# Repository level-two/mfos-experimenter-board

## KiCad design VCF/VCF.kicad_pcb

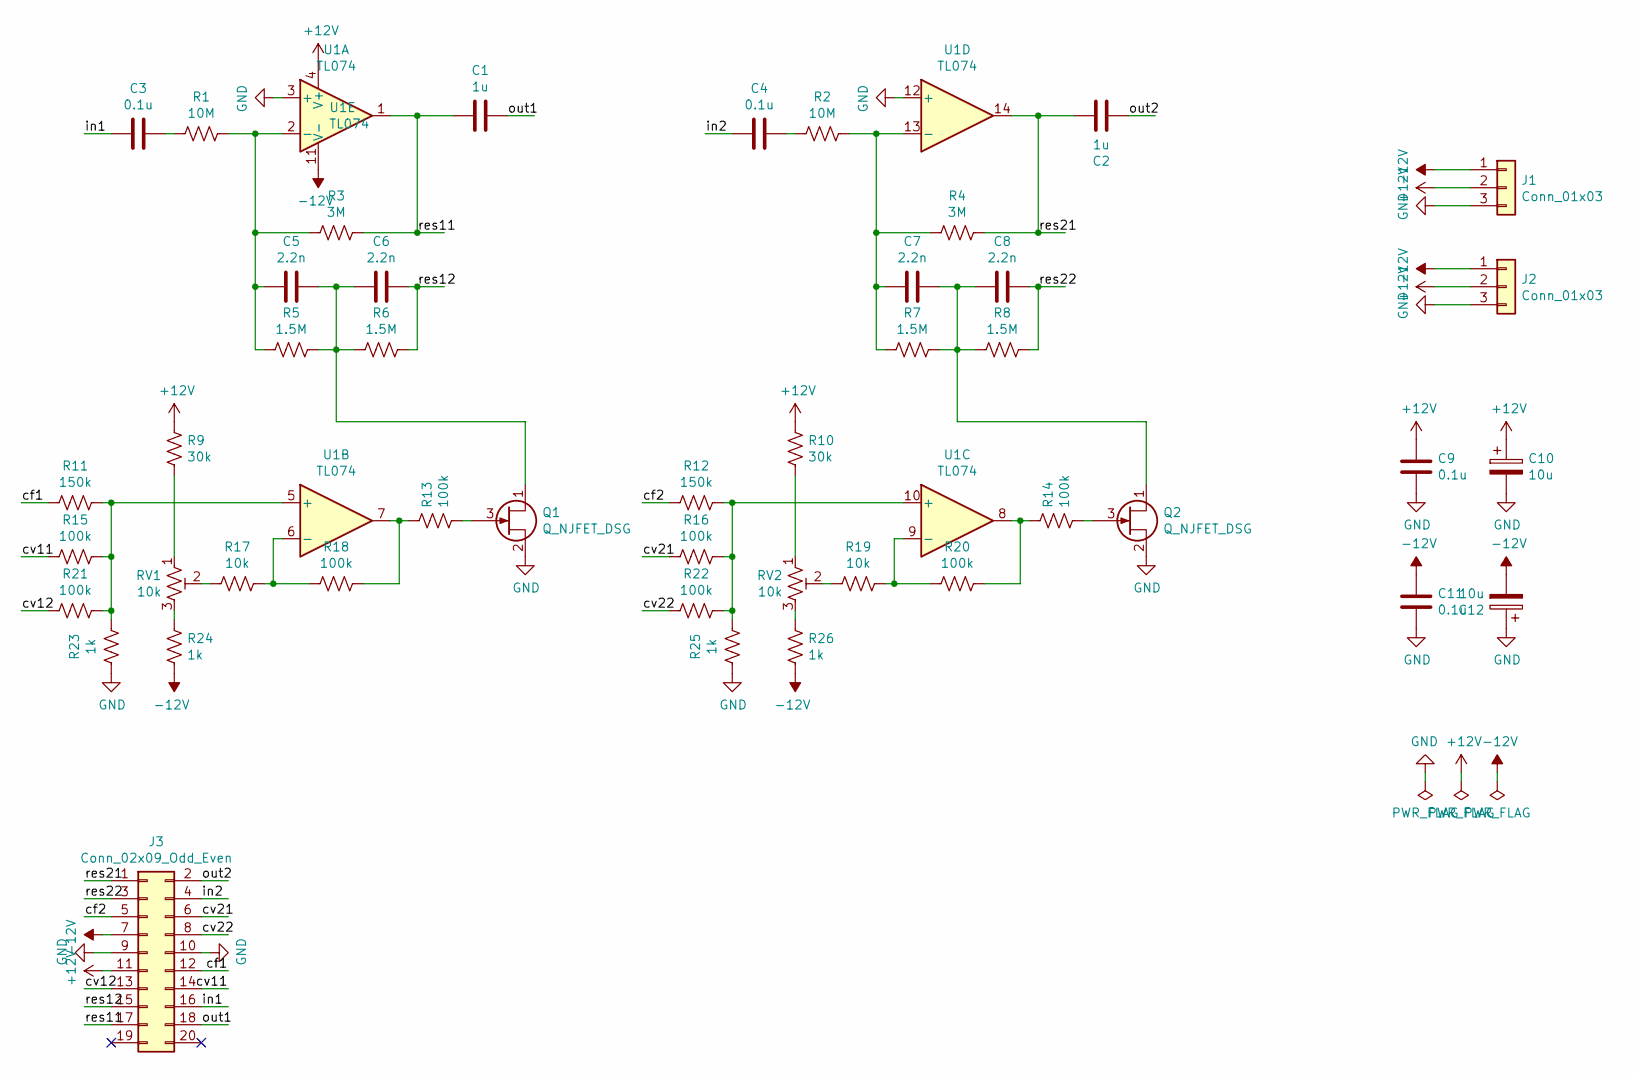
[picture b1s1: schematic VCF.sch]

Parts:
C1, C2: 1u; C_0603_1608Metric
C3, C4, C9, C11: 0.1u; C_0603_1608Metric
C5, C6, C7, C8: 2.2n; C_0402_1005Metric
C10, C12: 10u; C_Elec_6.3x5.4
J1, J2: Conn_01x03; PinHeader_1x03_P2.54mm_Horizontal
J3: Conn_02x09_Odd_Even; PinHeader_2x10_P2.54mm_Horizontal
Q1, Q2: Q_NJFET_DSG; TSOT-23
R1, R2: 10M; R_0402_1005Metric
R3, R4: 3M; R_0402_1005Metric
R5, R6, R7, R8: 1.5M; R_0402_1005Metric
R9, R10: 30k; R_0402_1005Metric
R11, R12: 150k; R_0402_1005Metric
R13, R14, R15, R16, R18, R20, R21, R22: 100k; R_0402_1005Metric
R17, R19: 10k; R_0402_1005Metric
R23, R24, R25, R26: 1k; R_0402_1005Metric
RV1, RV2: 10k; 3302
U1: TL074; SOIC-14_3.9x8.7mm_P1.27mm

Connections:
+12V: C9.1, C10.1, J1.2, J2.2, J3.11, R9.1, R10.1, U1.4 (V+)
-12V: C11.1, C12.2, J1.1, J2.1, J3.7, R24.2, R26.2, U1.11 (V-)
/cf1: J3.12, R11.2
/cf2: J3.5, R12.2
/cv11: J3.14, R15.2
/cv12: J3.13, R21.2
/cv21: J3.6, R16.2
/cv22: J3.8, R22.2
/in1: C3.2, J3.16
/in2: C4.2, J3.4
/out1: C1.1, J3.18
/out2: C2.1, J3.2
/res11: C1.2, J3.17, R3.1, U1.1
/res12: C6.1, J3.15, R6.1
/res21: C2.2, J3.1, R4.1, U1.14
/res22: C8.1, J3.3, R8.1
GND: C9.2, C10.2, C11.2, C12.1, J1.3, J2.3, J3.9, J3.10, Q1.2 (S), Q2.2 (S), R23.2, R25.2, U1.3 (+), U1.12 (+)
unnamed: C3.1, R1.2
unnamed: C4.1, R2.2
unnamed: C5.1, C6.2, Q1.1 (D), R5.1, R6.2
unnamed: C5.2, R1.1, R3.2, R5.2, U1.2 (-)
unnamed: C7.1, C8.2, Q2.1 (D), R7.1, R8.2
unnamed: C7.2, R2.1, R4.2, R7.2, U1.13 (-)
unnamed: Q1.3 (G), R13.2
unnamed: Q2.3 (G), R14.2
unnamed: R9.2, RV1.1
unnamed: R10.2, RV2.1
unnamed: R11.1, R15.1, R21.1, R23.1, U1.5 (+)
unnamed: R12.1, R16.1, R22.1, R25.1, U1.10 (+)
unnamed: R13.1, R18.2, U1.7
unnamed: R14.1, R20.2, U1.8
unnamed: R17.1, RV1.2
unnamed: R17.2, R18.1, U1.6 (-)
unnamed: R19.1, RV2.2
unnamed: R19.2, R20.1, U1.9 (-)
unnamed: R24.1, RV1.3
unnamed: R26.1, RV2.3

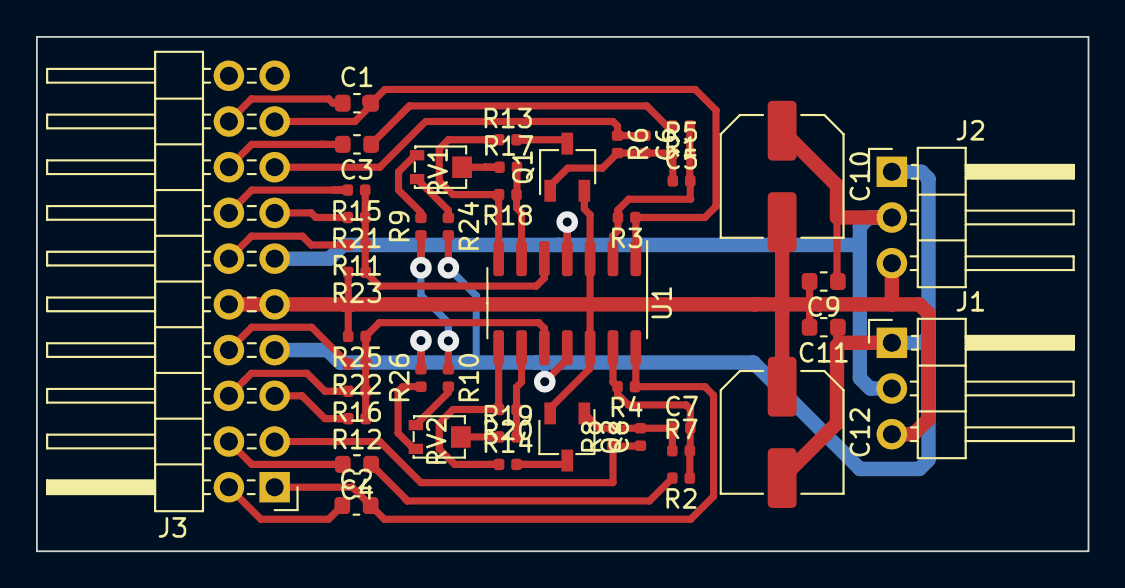
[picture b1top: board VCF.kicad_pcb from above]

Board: 2 copper layers, 58.4 x 28.6 mm, 46 parts (0 on the bottom side), 37 nets.

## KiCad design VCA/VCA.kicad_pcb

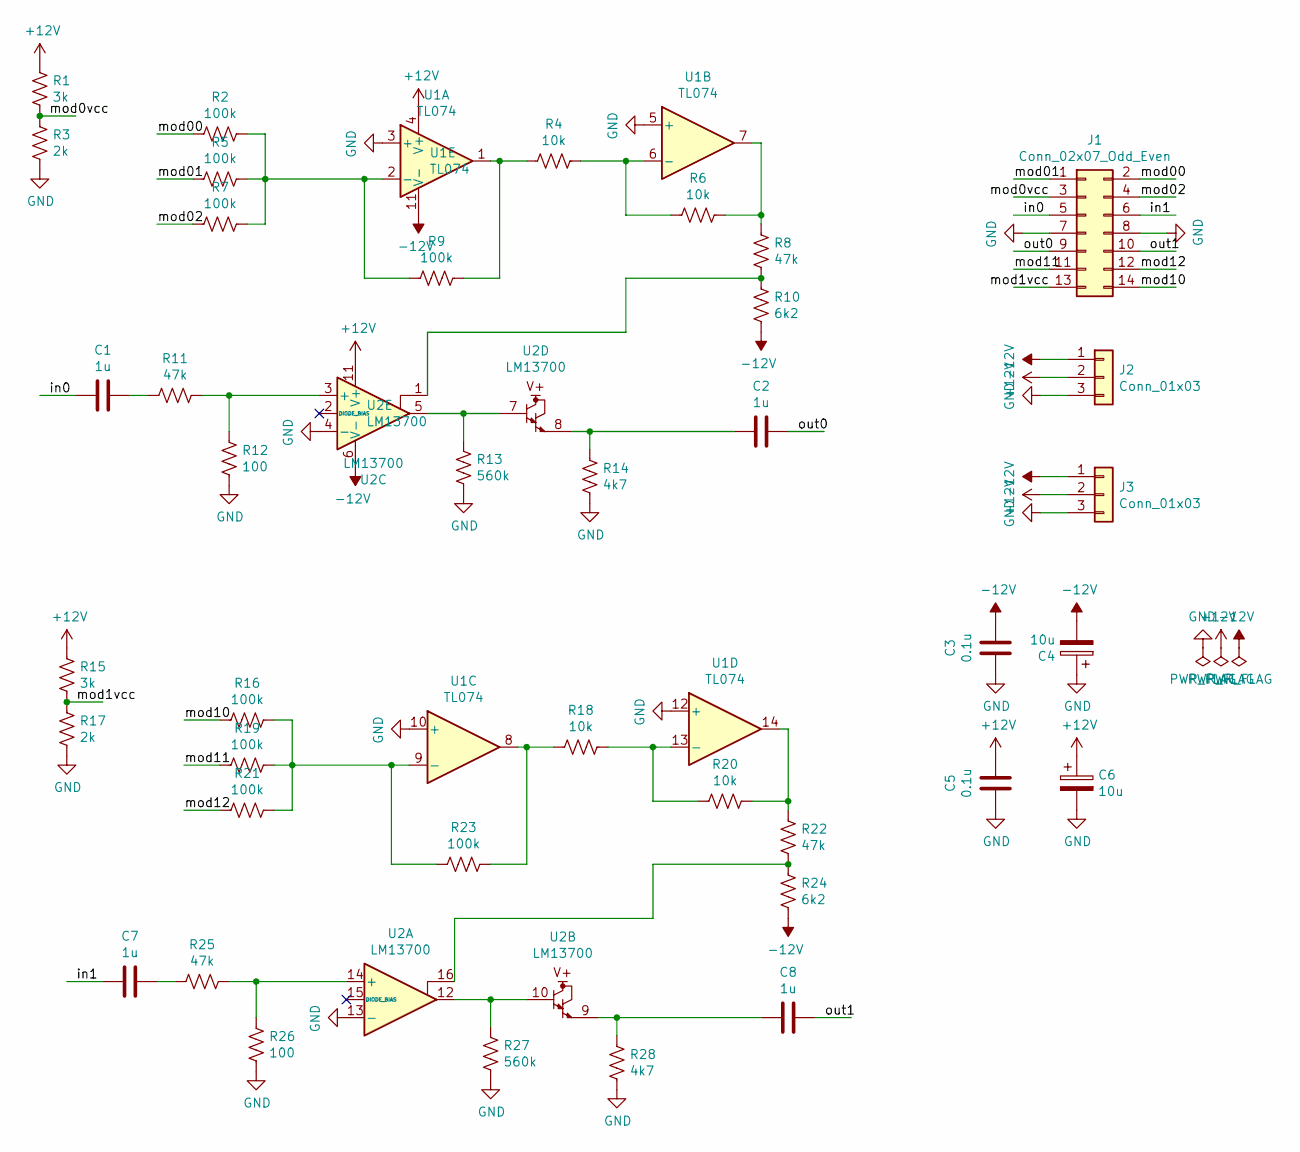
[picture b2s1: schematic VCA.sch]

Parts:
C1, C2, C7, C8: 1u; C_0603_1608Metric
C3, C5: 0.1u; C_0603_1608Metric
C4, C6: 10u; CP_Elec_6.3x5.4
J1: Conn_02x07_Odd_Even; IDC-Header_2x07_P2.54mm_Horizontal
J2, J3: Conn_01x03; PinHeader_1x03_P2.54mm_Horizontal
R1, R15: 3k; R_0402_1005Metric
R2, R5, R7, R9, R16, R19, R21, R23: 100k; R_0402_1005Metric
R3, R17: 2k; R_0402_1005Metric
R4, R6, R18, R20: 10k; R_0402_1005Metric
R8, R11, R22, R25: 47k; R_0402_1005Metric
R10, R24: 6k2; R_0402_1005Metric
R12, R26: 100; R_0402_1005Metric
R13, R27: 560k; R_0402_1005Metric
R14, R28: 4k7; R_0402_1005Metric
U1: TL074; SOIC-14_3.9x8.7mm_P1.27mm
U2: LM13700; DIP-16_W7.62mm

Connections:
+12V: C5.1, C6.1, J2.2, J3.2, R1.1, R15.1, U1.4 (V+), U2.11 (V+)
-12V: C3.1, C4.2, J2.1, J3.1, R10.2, R24.2, U1.11 (V-), U2.6 (V-)
/in0: C1.2, J1.5
/in1: C7.2, J1.6
/mod00: J1.2, R2.1
/mod0vcc: J1.3, R1.2, R3.1
/mod01: J1.1, R5.1
/mod1vcc: J1.13, R15.2, R17.1
/mod02: J1.4, R7.1
/mod10: J1.14, R16.1
/mod11: J1.11, R19.1
/mod12: J1.12, R21.1
/out0: C2.1, J1.9
/out1: C8.1, J1.10
GND: C3.2, C4.1, C5.2, C6.2, J1.7, J1.8, J2.3, J3.3, R3.2, R12.1, R13.2, R14.2, R17.2, R26.1, R27.2, R28.2, U1.3 (+), U1.5 (+), U1.10 (+), U1.12 (+), U2.4 (-), U2.13 (-)
unnamed: C1.1, R11.1
unnamed: C2.2, R14.1, U2.8
unnamed: C7.1, R25.1
unnamed: C8.2, R28.1, U2.9
unnamed: R2.2, R5.2, R7.2, R9.1, U1.2 (-)
unnamed: R4.1, R9.2, U1.1
unnamed: R4.2, R6.1, U1.6 (-)
unnamed: R6.2, R8.1, U1.7
unnamed: R8.2, R10.1, U2.1
unnamed: R11.2, R12.2, U2.3 (+)
unnamed: R13.1, U2.5, U2.7
unnamed: R16.2, R19.2, R21.2, R23.1, U1.9 (-)
unnamed: R18.1, R23.2, U1.8
unnamed: R18.2, R20.1, U1.13 (-)
unnamed: R20.2, R22.1, U1.14
unnamed: R22.2, R24.1, U2.16
unnamed: R25.2, R26.2, U2.14 (+)
unnamed: R27.1, U2.10, U2.12

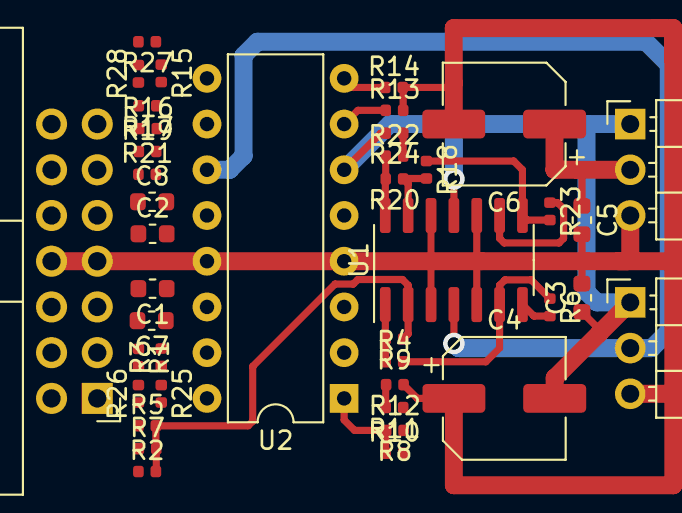
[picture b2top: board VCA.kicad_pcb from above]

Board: 2 copper layers, 41 parts (0 on the bottom side), 33 nets.

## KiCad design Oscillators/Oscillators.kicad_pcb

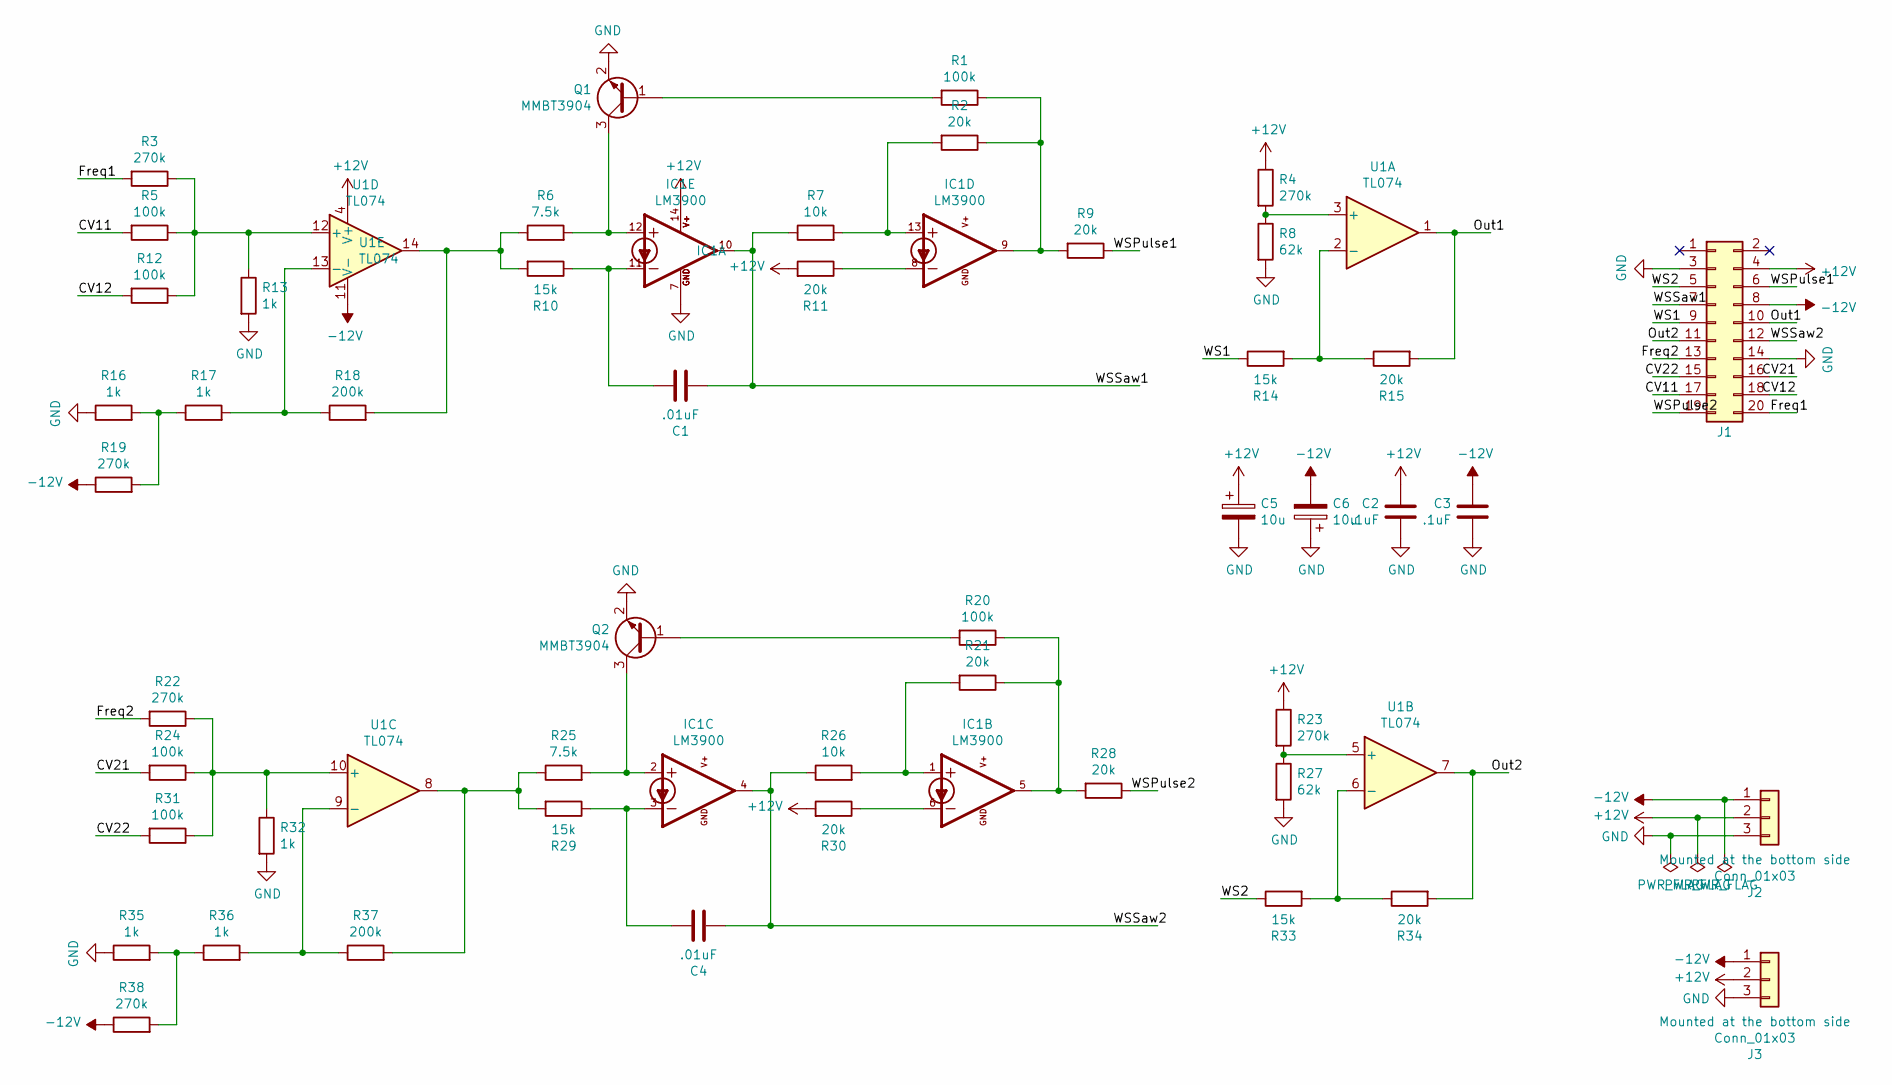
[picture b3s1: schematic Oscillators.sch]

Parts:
C1, C4: .01uF; C_0402_1005Metric
C2, C3: .1uF; C_0603_1608Metric
C5, C6: 10u; C_Elec_6.3x5.4
IC1: LM3900; SOIC-14_3.9x8.7mm_P1.27mm
J1: Conn_02x09_Odd_Even; PinHeader_2x10_P2.54mm_Horizontal
J2, J3: Conn_01x03; PinSocket_1x03_P2.54mm_Horizontal
Q1, Q2: MMBT3904; SOT-23
R1, R5, R12, R20, R24, R31: 100k; R_0402_1005Metric
R2, R9, R11, R15, R21, R28, R30, R34: 20k; R_0402_1005Metric
R3, R4, R19, R22, R23, R38: 270k; R_0402_1005Metric
R6, R25: 7.5k; R_0402_1005Metric
R7, R26: 10k; R_0402_1005Metric
R8, R27: 62k; R_0402_1005Metric
R10, R14, R29, R33: 15k; R_0402_1005Metric
R13, R16, R17, R32, R35, R36: 1k; R_0402_1005Metric
R18, R37: 200k; R_0402_1005Metric
U1: TL074; SOIC-14_3.9x8.7mm_P1.27mm

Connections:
+12V: C2.2, C5.1, IC1.14 (V+), J1.4, J2.2, J3.2, R4.1, R11.2, R23.1, R30.2, U1.4 (V+)
-12V: C3.2, C6.2, J1.8, J2.1, J3.1, R19.1, R38.1, U1.11 (V-)
/CV11: J1.17, R5.2
/CV12: J1.18, R12.2
/CV21: J1.16, R24.2
/CV22: J1.15, R31.2
/Freq1: J1.20, R3.2
/Freq2: J1.13, R22.2
/Out1: J1.10, R15.2, U1.1
/Out2: J1.11, R34.2, U1.7
/WS1: J1.9, R14.1
/WS2: J1.5, R33.1
/WSPulse1: J1.6, R9.1
/WSPulse2: J1.19, R28.1
/WSSaw1: C1.2, IC1.10 (OUT), J1.7, R7.1
/WSSaw2: C4.2, IC1.4 (OUT), J1.12, R26.1
GND: C2.1, C3.1, C5.2, C6.1, IC1.7 (GND), J1.3, J1.14, J2.3, J3.3, Q1.2 (E), Q2.2 (E), R8.2, R13.2, R16.1, R27.2, R32.2, R35.1
unnamed: C1.1, IC1.11 (-IN), R10.1
unnamed: C4.1, IC1.3 (-IN), R29.1
unnamed: IC1.1 (+IN), R21.2, R26.2
unnamed: IC1.2 (+IN), Q2.3 (C), R25.2
unnamed: IC1.5 (OUT), R20.1, R21.1, R28.2
unnamed: IC1.6 (-IN), R30.1
unnamed: IC1.8 (-IN), R11.1
unnamed: IC1.9 (OUT), R1.1, R2.1, R9.2
unnamed: IC1.12 (+IN), Q1.3 (C), R6.2
unnamed: IC1.13 (+IN), R2.2, R7.2
unnamed: Q1.1 (B), R1.2
unnamed: Q2.1 (B), R20.2
unnamed: R4.2, R8.1, U1.3 (+)
unnamed: R6.1, R10.2, R18.2, U1.14
unnamed: R3.1, R5.1, R12.1, R13.1, U1.12 (+)
unnamed: R14.2, R15.1, U1.2 (-)
unnamed: R16.2, R17.1, R19.2
unnamed: R17.2, R18.1, U1.13 (-)
unnamed: R22.1, R24.1, R31.1, R32.1, U1.10 (+)
unnamed: R23.2, R27.1, U1.5 (+)
unnamed: R25.1, R29.2, R37.2, U1.8
unnamed: R33.2, R34.1, U1.6 (-)
unnamed: R35.2, R36.1, R38.2
unnamed: R36.2, R37.1, U1.9 (-)

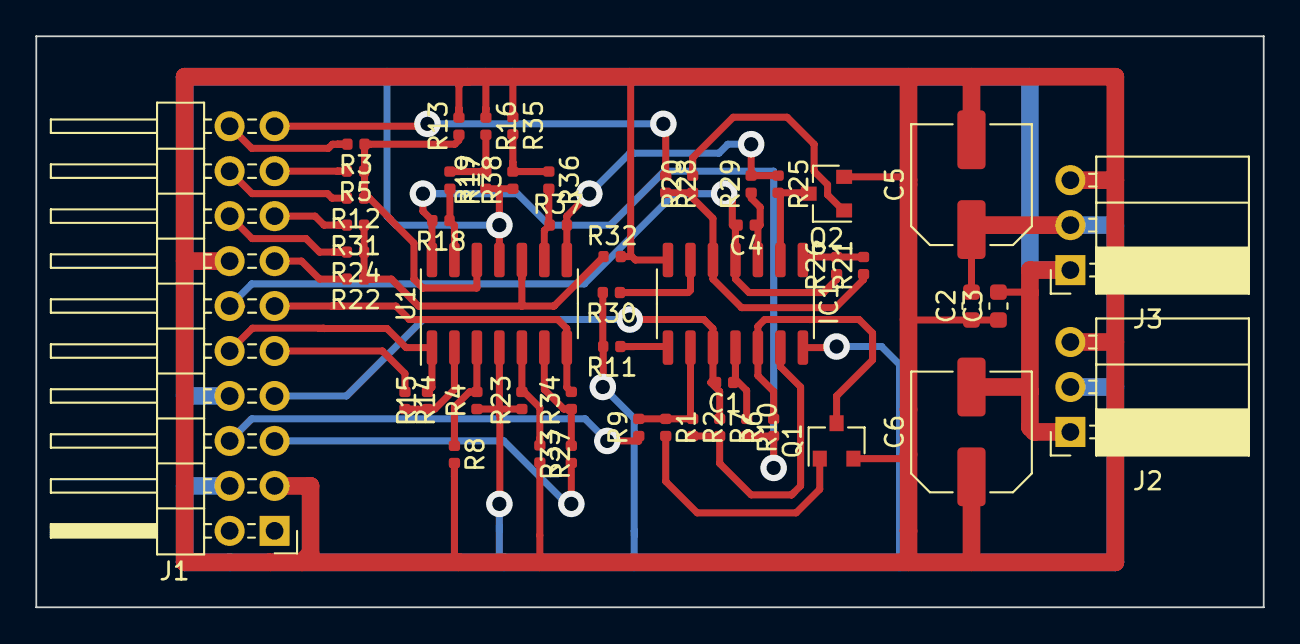
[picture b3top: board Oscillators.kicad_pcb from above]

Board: 2 copper layers, 69.3 x 32.3 mm, 51 parts (0 on the bottom side), 41 nets.

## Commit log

2019-11-01 Removed extra files from source control Updated .gitignore
2019-11-26 Oscillators PCB
2019-11-27 PCB components placement and routing - v2
2019-12-02 Two oscillators on single board sharing two chips
2019-12-10 Another board variant
2019-12-10 Cooler PCB version
2019-12-12 PCB cleaned from DRC warnings
2019-12-16 - Schematics - Components Documentation - PCB
2019-12-28 VCF Implementation
2019-12-29 VCF final version
2020-01-01 Oscillators PCB reworked
2020-01-02 - Updated connector wiring on schematic - New layout
2020-01-03 Oscillators PCB draft
2020-01-08 Oscillators board final version
2020-01-13 Updated VCF PCB using 0402 R/C components
2020-01-13 0603 capacitors for 0.1u and 1u as they are operating at dV > 10V
2020-01-13 Oscillators: - Changed R/C components to 0402 - SMD transistors MMBT3904
2020-01-18 Updated VCF and Oscillators PCBs/Schematics
2020-01-20 VCF: - Fixed capacitor polarity Oscillators: - Deleted outdated note on schematics
2020-01-20 VCA: - Schematics implementation - Selected packages for all components
2020-01-21 VCA PCB: - Placed parts
2020-01-21 VCA PCB: - Dense component packing - Swapped some pins on connector
2020-01-21 PCB Routing draft
2020-06-29 vca changes
2021-01-18 Updated PCBs for print
